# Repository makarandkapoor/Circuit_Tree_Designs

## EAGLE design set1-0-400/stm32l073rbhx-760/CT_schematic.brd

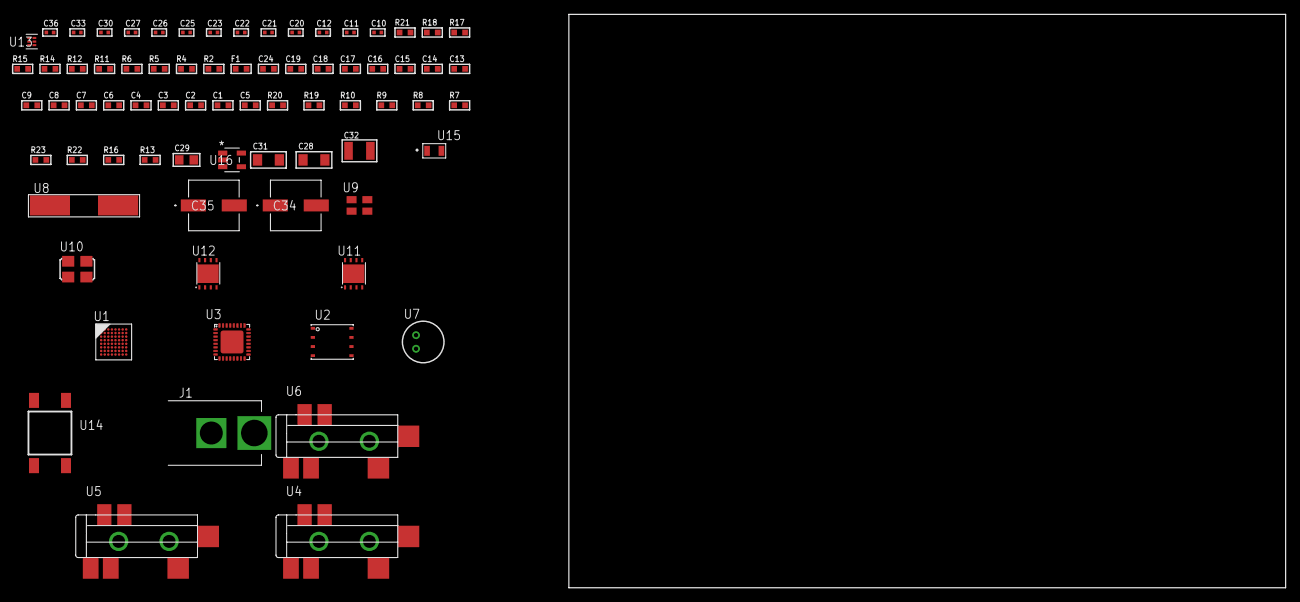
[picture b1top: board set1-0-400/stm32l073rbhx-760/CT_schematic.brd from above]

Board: 2 copper layers, 100.0 x 80.0 mm, 75 parts (0 on the bottom side), 44 nets, no tracks yet.

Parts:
C1, C2, C3, C4, C6, C9: 1e-07; C0603
C5: 4.7e-06; C0603
C7: 1e-08; C0603
C8, C13, C14, C15, C16, C17, C18, C19, C24: 1e-06; C0603
C10, C11: 1e-11; C0402
C12, C25, C26, C27, C30, C36: 1e-08; C0402
C20, C21, C22, C23, C33: 1e-07; C0402
C28, C31: 1e-05; C1206
C29: 1e-05; C0805
C32: 1e-05; C1210
C34, C35: 0.0001; EXV-9H
F1: 240.0; L0603
J1: PJ-037B; PJ-037B_PACKAGE
R2, R15, R18: 1000.0; R0603
R4: 4700.0; R0603
R5, R6: 2200.0; R0603
R7, R8, R9, R10, R19, R20: 10000.0; R0603
R11, R12: 1270.0; R0603
R13, R16: 100000.0; R0603
R14: 200.0; R0603
R17: 2231.0; R0603
R21: 9100.0; R0603
R22: 680000.0; R0603
R23: 120000.0; R0603
U1: STM32L073RBH6; TFBGA64
U2: 24AA256-I/MF; DFN8-S
U3: SGTL5000XNAA3; QFN-32
U4, U5, U6: SJ-43515TS-SMT-TR
U7: WM-64PCT; WM-64PC
U8: ABLS-25.000MHZ-B2F-T
U9: ASEK-32.768KHz-ECST; ASEK
U10: ASFL-24.57MHZ-NCS; ASFL1
U11, U12: LP3878SDX-ADJ/NOPB; WSON-8
U13: TPS3895ADRYR; SON-6
U14: 4-1437565-2; SW_4-1437565-2
U15: Q65110A2395; LGM67K-G1J2-24-Z
U16: nc7sz125m5x; NC7SZ125M5X

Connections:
CLK_CRYSTAL_U1_C1: C10.1, U1.C1, U8.1
CLK_CRYSTAL_U1_D1: C11.1, U1.D1, U8.2
CLK_U1_A1: U1.A1, U9.3
CLK_U3_21: U3.21, U10.3
GND: C1.2, C2.2, C3.2, C4.2, C5.2, C6.2, C7.2, C8.2, C9.2, C10.2, C11.2, C12.2, C20.2, C21.2, C22.2, C23.2, C24.2, C25.2, C26.2, C27.2, C28.2, C29.2, C30.2, C31.2, C32.2, C33.2, C34.2, C35.2, C36.2, J1.2, R2.2, R7.2, R8.2, R9.2, R12.2, R15.2, R18.2, R21.2, R23.2, U1.C2, U1.D4, U1.D5, U1.D6, U1.F1, U2.4, U3.1, U3.3, U3.7, U3.EXP, U5.1, U6.1, U7.2, U9.2, U10.2, U11.3, U11.PAD, U12.3, U12.PAD, U13.2, U15.C, U16.1, U16.3
NET_U1_A3: R6.1, U1.A3, U2.5
NET_U1_B2: C6.1, U1.B2
NET_U1_B3: R5.1, U1.B3, U2.6
NET_U1_B4: R7.1, U1.B4
NET_U1_E1: R4.1, U1.E1, U16.4
NET_U1_H1: C7.1, C8.1, F1.1, U1.G1, U1.H1
NET_U1_H7: U14.3, U14.4
NET_U2_1: R8.1, U2.1
NET_U2_2: R9.1, U2.2
NET_U2_3: R10.1, U2.3
NET_U3_10: C23.1, U3.10
NET_U3_29: R11.1, U3.29
NET_U3_31: R12.1, U3.31
NET_U4_1: U3.4, U4.1
NET_U4_2: U3.2, U4.2
NET_U4_5: U3.6, U4.5
NET_U5_2: C14.1, U5.2
NET_U5_5: C13.1, U5.5
NET_U6_2: C16.1, C17.1, U6.2
NET_U6_5: C15.1, U6.5
NET_U6_13: C16.2, C17.2
NET_U7_1: C18.1, C19.1, C24.1, U3.16, U7.1
NET_U7_15: C18.2, C19.2
NET_U11_1: C27.1, U11.1
NET_U11_6: R14.2, R15.1, U11.6
NET_U11_8: R13.1, U11.8
NET_U12_1: C30.1, U12.1
NET_U12_6: R17.2, R18.1, U12.6
NET_U12_8: R16.1, U12.8
NET_U13_1: R20.1, R21.1, U13.1
NET_U13_3: R22.2, R23.1, U13.3
NET_U13_4: R19.1, U13.4, U16.2
NET_U14_1: R2.1, U14.1, U14.2
PROC_I2S2_CK: U1.G8, U3.24
PROC_I2S2_SD: U1.F7, U3.26
PROC_I2S2_WS: U1.H8, U3.23
VCC_S1_7V5: C28.1, C31.1, C34.1, C35.1, J1.1, R13.2, R16.2, U11.4, U12.4
VCC_TIER1_1V2: C20.1, C29.1, R14.1, U3.30, U11.5
VCC_TIER1_3V3: C1.1, C2.1, C3.1, C4.1, C5.1, C9.1, C12.1, C21.1, C22.1, C25.1, C26.1, C32.1, C33.1, C36.1, F1.2, R4.2, R5.2, R6.2, R10.2, R11.2, R17.1, R19.2, R20.2, R22.1, U1.D2, U1.E4, U1.E5, U1.E6, U2.7, U2.8, U3.5, U3.20, U9.4, U10.4, U12.5, U13.6, U16.5

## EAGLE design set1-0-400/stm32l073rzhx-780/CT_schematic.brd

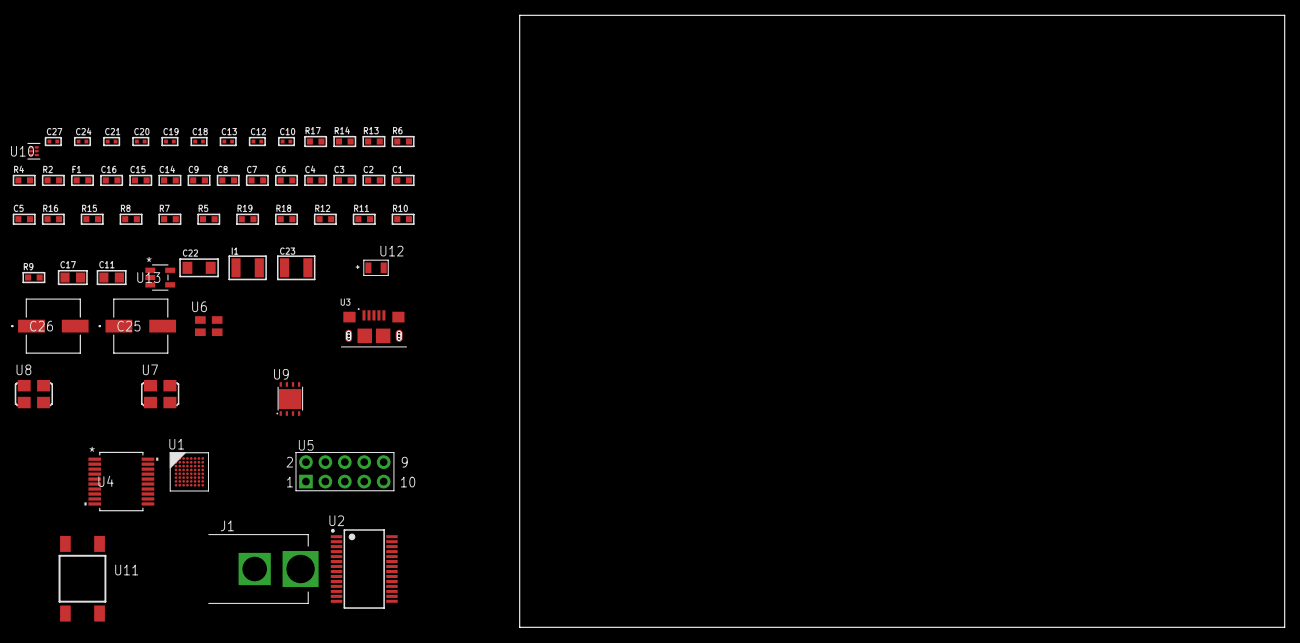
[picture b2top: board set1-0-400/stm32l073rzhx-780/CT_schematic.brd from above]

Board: 2 copper layers, 122.6 x 80.0 mm, 60 parts (0 on the bottom side), 44 nets, no tracks yet.

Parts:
C1, C2, C3, C4, C6, C9: 1e-07; C0603
C5: 4.7e-06; C0603
C7: 1e-08; C0603
C8, C14, C15, C16: 1e-06; C0603
C10, C12, C13, C24: 1e-07; C0402
C11, C17: 4.7e-06; C0805
C18, C19, C20, C21, C27: 1e-08; C0402
C22: 1e-05; C1206
C23: 1e-05; C1210
C25, C26: 0.0001; EXV-9H
F1: 240.0; L0603
I1: 1.5e-05; L1210
J1: PJ-037B; PJ-037B_PACKAGE
R2, R14: 1000.0; R0603
R4, R6: 4700.0; R0603
R5, R7, R8, R15, R16: 10000.0; R0603
R9, R10, R11, R12: 100000.0; R0603
R13: 2231.0; R0603
R17: 9100.0; R0603
R18: 680000.0; R0603
R19: 120000.0; R0603
U1: STM32L073RZH6; TFBGA64
U2: FT232RL-REEL; SSOP-28
U3: 10118193-0001LF; FCI_10118193-0001LF
U4: MAX3218EAP+T; SSOP-20
U5: HTSS-105-01-G-D
U6: ASEK-32.768KHz-ECST; ASEK
U7: ASFL1-12MHZ-NCS; ASFL1
U8: ASFL1-25MHZ-NCS; ASFL1
U9: LP3878SDX-ADJ/NOPB; WSON-8
U10: TPS3895ADRYR; SON-6
U11: 4-1437565-2; SW_4-1437565-2
U12: Q65110A2395; LGM67K-G1J2-24-Z
U13: nc7sz125m5x; NC7SZ125M5X

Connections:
CLK_U1_A1: U1.A1, U6.3
CLK_U1_C1: U1.C1, U8.3
CLK_U2_27: U2.27, U7.3
GND: C1.2, C2.2, C3.2, C4.2, C5.2, C6.2, C7.2, C8.2, C9.2, C10.2, C11.2, C12.2, C13.2, C14.2, C15.2, C16.2, C18.2, C19.2, C20.2, C21.2, C22.2, C23.2, C24.2, C25.2, C26.2, C27.2, J1.2, R2.2, R5.2, R8.2, R14.2, R17.2, R19.2, U1.C2, U1.D4, U1.D5, U1.D6, U1.F1, U2.7, U2.18, U2.21, U2.25, U2.26, U3.5, U3.6, U3.7, U3.8, U3.9, U4.5, U4.17, U4.20, U5.9, U6.2, U7.2, U8.2, U9.3, U9.PAD, U10.2, U12.C, U13.1, U13.3
NET_U1_B2: C6.1, U1.B2
NET_U1_B4: R5.1, U1.B4
NET_U1_E1: R4.1, U1.E1, U13.4
NET_U1_H1: C7.1, C8.1, F1.1, U1.G1, U1.H1
NET_U1_H8: U11.3, U11.4
NET_U2_14: R7.1, U2.14
NET_U2_17: C12.1, U2.17
NET_U2_19: R8.1, U2.19
NET_U3_1: R6.1, U3.1
NET_U3_2: U2.16, U3.2
NET_U3_3: U2.15, U3.3
NET_U4_1: I1.1, U4.1
NET_U4_2: R9.1, U4.2
NET_U4_3: R10.1, U4.3
NET_U4_4: R11.1, U4.4
NET_U4_15: C16.1, U4.15
NET_U4_16: C17.2, U4.16
NET_U4_18: C17.1, U4.18
NET_U4_19: C15.1, U4.19
NET_U5_3: U4.12, U5.3
NET_U5_4: U4.11, U5.4
NET_U5_5: U4.14, U5.5
NET_U5_6: U4.13, U5.6
NET_U9_1: C21.1, U9.1
NET_U9_6: R13.2, R14.1, U9.6
NET_U9_8: R12.1, U9.8
NET_U10_1: R16.1, R17.1, U10.1
NET_U10_3: R18.2, R19.1, U10.3
NET_U10_4: R15.1, U10.4, U13.2
NET_U11_1: R2.1, U11.1, U11.2
PROC_LPUART1_CTS: U1.G4, U4.8
PROC_LPUART1_RTS: U1.B5, U4.10
PROC_LPUART1_RX: U1.A8, U4.9
PROC_LPUART1_TX: U1.A7, U4.7
PROC_USART1_CTS: U1.A4, U2.3
PROC_USART1_RTS: U1.A5, U2.11
PROC_USART1_RX: U1.C3, U2.1
PROC_USART1_TX: U1.C7, U2.5
VCC_S1_6V6: C22.1, C25.1, C26.1, J1.1, R12.2, U9.4
VCC_TIER1_3V3: C1.1, C2.1, C3.1, C4.1, C5.1, C9.1, C10.1, C11.1, C13.1, C14.1, C18.1, C19.1, C20.1, C23.1, C24.1, C27.1, F1.2, I1.2, R4.2, R7.2, R9.2, R10.2, R11.2, R13.1, R15.2, R16.2, R18.1, U1.D2, U1.E4, U1.E5, U1.E6, U2.4, U2.20, U4.6, U6.4, U7.4, U8.4, U9.5, U10.6, U13.5

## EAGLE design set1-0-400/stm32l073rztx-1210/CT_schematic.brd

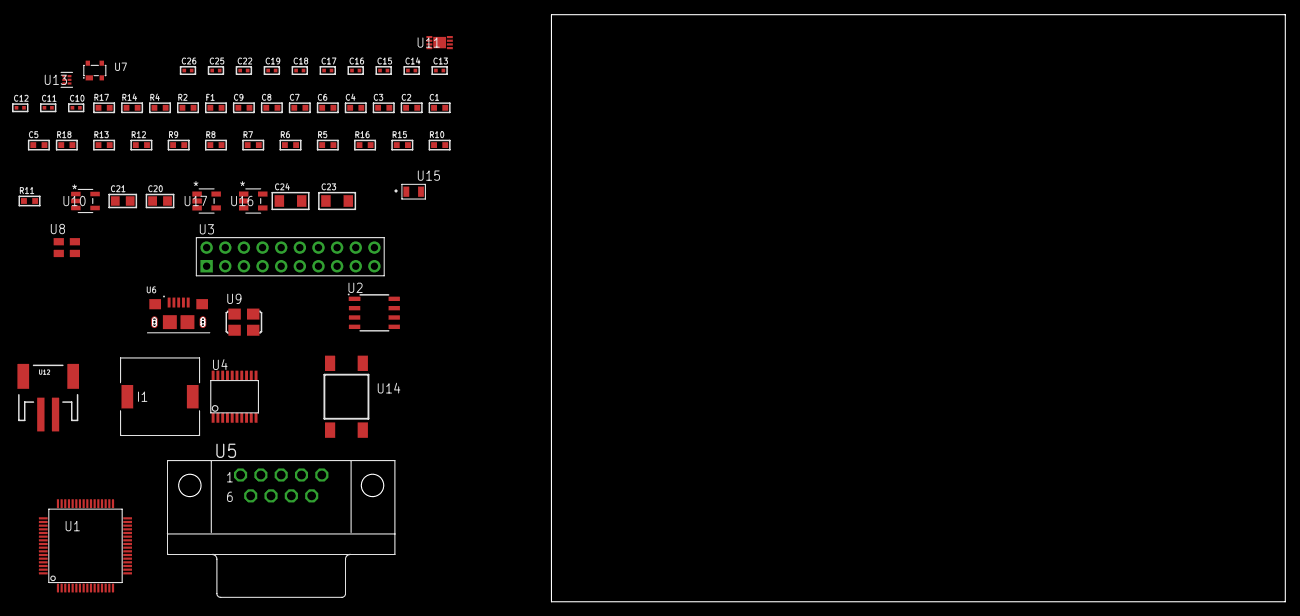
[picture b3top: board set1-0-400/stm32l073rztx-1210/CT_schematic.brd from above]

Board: 2 copper layers, 61 parts (0 on the bottom side), 45 nets, no tracks yet.

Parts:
C1, C2, C3, C4, C6, C9: 1e-07; C0603
C5: 4.7e-06; C0603
C7: 1e-08; C0603
C8: 1e-06; C0603
C10, C18, C19, C25, C26: 1e-08; C0402
C11, C12, C13, C14, C15, C16, C17, C22: 1e-07; C0402
C20, C21: 1e-05; C0805
C23, C24: 1e-05; C1206
F1: 240.0; L0603
I1: 5.2e-06; DR1040
R2: 1000.0; R0603
R4: 4700.0; R0603
R5, R6, R7, R8, R9, R12, R13, R18: 10000.0; R0603
R10: 220000.0; R0603
R11: 1000000.0; R0603
R14: 9100.0; R0603
R15: 680000.0; R0603
R16: 120000.0; R0603
R17: 2000.0; R0603
U1: STM32L073RZT6; LQFP64
U2: AT25128B-SSHL-T; SOIC-8
U3: TST-110-05-T-D-RA
U4: SP3203ECY-L/TR; TSSOP20-I
U5: 182-009-113R531; 182-009-MALE
U6: 10118193-0001LF; FCI_10118193-0001LF
U7: prtr5v0u2ax; SOT143B
U8: ASEK-32.768KHz-ECST; ASEK
U9: ASFL1-25MHZ-NCS; ASFL1
U10: ltc3406es5; TSOT-23-5
U11: MCP73831T-2ACI/MC; DFN8_2X3MC
U12: S2B-PH-SM4-TB(LF)(SN); JST-2-SMD
U13: TPS3895ADRYR; SON-6
U14: 4-1437565-2; SW_4-1437565-2
U15: Q65110A2395; LGM67K-G1J2-24-Z
U16, U17: nc7sz125m5x; NC7SZ125M5X

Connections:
CLK_U1_3: U1.3, U8.3
CLK_U1_5: U1.5, U9.3
GND: C1.2, C2.2, C3.2, C4.2, C5.2, C6.2, C7.2, C8.2, C9.2, C10.2, C11.2, C12.2, C13.2, C16.2, C17.2, C18.2, C19.2, C20.2, C21.1, C21.2, C22.2, C23.2, C24.2, C25.2, C26.2, R2.2, R5.2, R10.2, R14.2, R16.2, R17.2, U1.12, U1.18, U1.31, U1.47, U1.63, U2.4, U3.4, U3.6, U3.8, U3.10, U3.12, U3.14, U3.16, U3.18, U3.20, U4.18, U5.5, U6.5, U6.6, U6.7, U6.8, U6.9, U7.1, U8.2, U9.2, U10.2, U11.6, U11.9, U12.2, U13.2, U15.C, U16.2, U16.3, U17.1, U17.3
INPUT_USBPOWER_5V: C23.1, R18.2, U6.1, U7.4, U11.1, U11.2
NET_U1_1: C6.1, U1.1
NET_U1_7: R4.1, U1.7, U17.4
NET_U1_13: C7.1, C8.1, F1.1, U1.13
NET_U1_60: R5.1, U1.60
NET_U1_62: U14.3, U14.4
NET_U2_3: R6.1, U2.3
NET_U2_7: R8.1, U2.7
NET_U4_1: C14.1, U4.1
NET_U4_2: C16.1, U4.2
NET_U4_3: C14.2, U4.3
NET_U4_4: C15.1, U4.4
NET_U4_5: C15.2, U4.5
NET_U4_6: C17.1, U4.6
NET_U5_2: U4.14, U5.2
NET_U5_3: U4.17, U5.3
NET_U5_7: U4.13, U5.7
NET_U5_8: U4.16, U5.8
NET_U10_3: I1.1, U10.3
NET_U10_5: R10.1, R11.1, U10.5
NET_U10_ATNET_3: I1.2, R11.2
NET_U11_5: R18.1, U11.5
NET_U11_8: R17.1, U11.8
NET_U13_1: R13.1, R14.1, U13.1
NET_U13_3: R15.2, R16.1, U13.3
NET_U13_4: R12.1, U13.4, U16.4, U17.2
NET_U14_1: R2.1, U14.1, U14.2
PROC_LPUART1_CTS: U1.22, U4.8
PROC_LPUART1_RTS: U1.27, U4.10
PROC_LPUART1_RX: U1.8, U4.11
PROC_LPUART1_TX: U1.9, U4.7
PROC_SPI1_MISO: U1.56, U2.2
PROC_SPI1_MOSI: U1.23, U2.5
PROC_SPI1_NSS: R7.1, U1.20, U2.1
PROC_SPI1_SCK: U1.21, U2.6
PROC_SYS_SWCLK: U1.49, U3.9
PROC_SYS_SWDIO: U1.46, U3.7
PROC_USB_DM: U6.2, U7.3
PROC_USB_DP: U6.3, U7.2
RST_OUT_U3_SRESET_B: R9.1, U3.15, U16.1
VCC_S1_3V7: C20.1, C24.1, U10.4, U11.3, U11.4, U12.1
VCC_TIER1_3V3: C1.1, C2.1, C3.1, C4.1, C5.1, C9.1, C10.1, C11.1, C12.1, C13.1, C18.1, C19.1, C21.2, C22.1, C25.1, C26.1, F1.2, I1.2, R4.2, R6.2, R7.2, R8.2, R9.2, R11.2, R12.2, R13.2, R15.1, U1.19, U1.32, U1.48, U1.64, U2.8, U3.1, U4.12, U4.19, U8.4, U9.4, U13.6, U16.5, U17.5

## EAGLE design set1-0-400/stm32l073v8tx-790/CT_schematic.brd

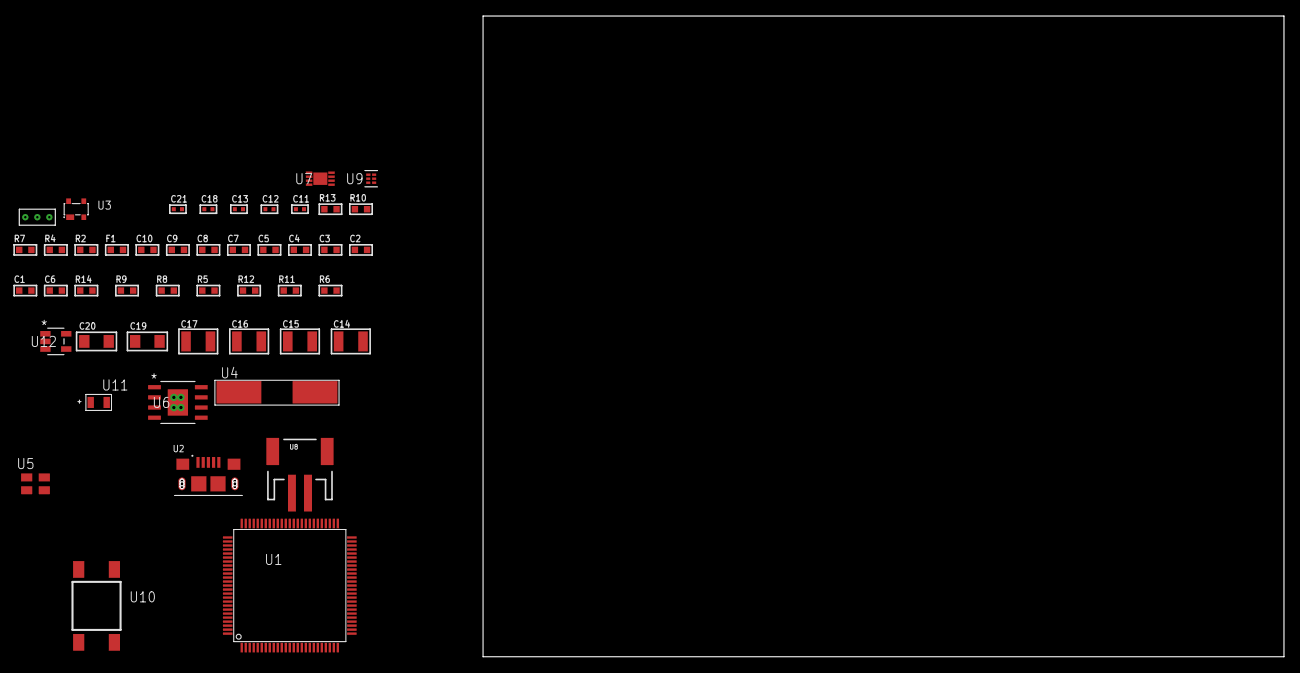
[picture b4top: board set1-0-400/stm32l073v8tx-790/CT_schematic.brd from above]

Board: 2 copper layers, 47 parts (0 on the bottom side), 23 nets, no tracks yet.

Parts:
C1, C2, C3, C4, C5, C7, C10: 1e-07; C0603
C6: 4.7e-06; C0603
C8: 1e-08; C0603
C9: 1e-06; C0603
C11, C12: 1e-11; C0402
C13, C21: 1e-08; C0402
C14, C15, C16, C17: 1e-05; C1210
C18: 1e-07; C0402
C19, C20: 1e-05; C1206
F1: 240.0; L0603
R2: 1000.0; R0603
R4: 4700.0; R0603
R5, R8, R9, R14: 10000.0; R0603
R6: 4031.5447154472; R0603
R7: 2200.0; R0603
R10: 9100.0; R0603
R11: 680000.0; R0603
R12: 120000.0; R0603
R13: 2000.0; R0603
U1: STM32L073V8T6; LQFP100
U2: 10118193-0001LF; FCI_10118193-0001LF
U3: prtr5v0u2ax; SOT143B
U4: ABLS-25.000MHZ-B2F-T
U5: ASEK-32.768KHz-ECST; ASEK
U6: MIC5234YME; SOIC-8_EP
U7: MCP73831T-2ACI/MC; DFN8_2X3MC
U8: S2B-PH-SM4-TB(LF)(SN); JST-2-SMD
U9: TPS3895ADRYR; SON-6
U10: 4-1437565-2; SW_4-1437565-2
U11: Q65110A2395; LGM67K-G1J2-24-Z
U12: nc7sz125m5x; NC7SZ125M5X
U13: Dummy; DUMMY_PACKAGE_102

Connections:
CLK_CRYSTAL_U1_12: C11.1, U1.12, U4.1
CLK_CRYSTAL_U1_13: C12.1, U1.13, U4.2
CLK_U1_8: U1.8, U5.3
GND: C1.2, C2.2, C3.2, C4.2, C5.2, C6.2, C7.2, C8.2, C9.2, C10.2, C11.2, C12.2, C13.2, C14.2, C15.2, C16.2, C17.2, C18.2, C19.2, C20.2, C21.2, R2.2, R5.2, R7.2, R10.2, R12.2, R13.2, U1.19, U1.20, U1.27, U1.49, U1.74, U1.99, U2.5, U2.6, U2.7, U2.8, U2.9, U3.1, U5.2, U6.7, U6.EPAD, U7.6, U7.9, U8.2, U9.2, U11.C, U12.1, U12.3, U13.1
INPUT_USBPOWER_5V: C19.1, R14.2, U2.1, U3.4, U7.1, U7.2
NET_U1_6: C7.1, U1.6
NET_U1_14: R4.1, U1.14, U12.4
NET_U1_22: C8.1, C9.1, F1.1, U1.21, U1.22
NET_U1_94: R5.1, U1.94
NET_U1_98: U10.3, U10.4
NET_U6_4: R6.2, R7.1, U6.4
NET_U7_5: R14.1, U7.5
NET_U7_8: R13.1, U7.8
NET_U9_1: R9.1, R10.1, U9.1
NET_U9_3: R11.2, R12.1, U9.3
NET_U9_4: R8.1, U9.4, U12.2
NET_U10_1: R2.1, U10.1, U10.2
PROC_ADC_IN3: U1.26, U13.3
PROC_ADC_IN13: U1.18, U13.2
PROC_USB_DM: U1.70, U2.2, U3.3
PROC_USB_DP: U1.71, U2.3, U3.2
VCC_S1_3V7: C14.1, C15.1, C20.1, U6.5, U6.8, U7.3, U7.4, U8.1
VCC_TIER1_3V3: C1.1, C2.1, C3.1, C4.1, C5.1, C6.1, C10.1, C13.1, C16.1, C17.1, C18.1, C21.1, F1.2, R4.2, R6.1, R8.2, R9.2, R11.1, U1.28, U1.50, U1.73, U1.75, U1.100, U5.4, U6.1, U9.6, U12.5

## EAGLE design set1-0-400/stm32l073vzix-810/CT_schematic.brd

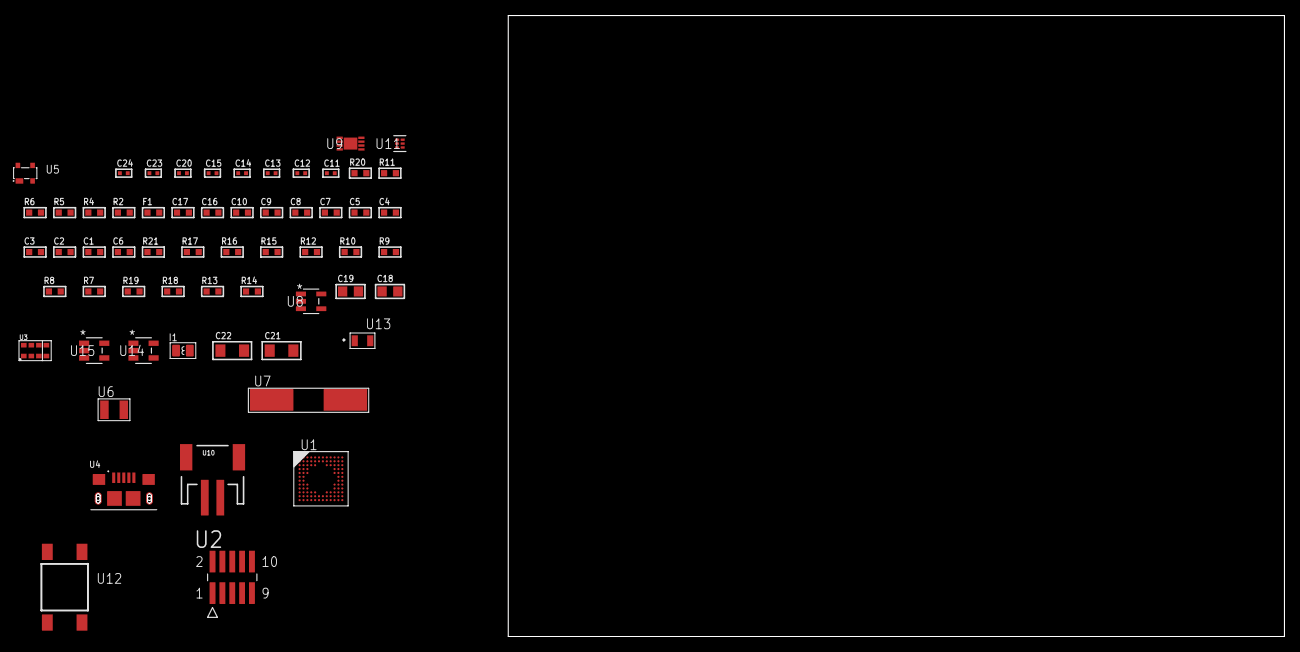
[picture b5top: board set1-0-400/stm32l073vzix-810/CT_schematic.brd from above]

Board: 2 copper layers, 153.1 x 80.0 mm, 60 parts (0 on the bottom side), 31 nets, no tracks yet.

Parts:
C1, C2, C3, C4, C5, C7, C10: 1e-07; C0603
C6: 4.7e-06; C0603
C8: 1e-08; C0603
C9, C16, C17: 1e-06; C0603
C11, C12, C13, C14: 1e-11; C0402
C15, C20: 1e-07; C0402
C18, C19: 1e-05; C0805
C21, C22: 1e-05; C1206
C23, C24: 1e-08; C0402
F1: 240.0; L0603
I1: 3.3e-06; L0806
R2: 1000.0; R0603
R4: 4700.0; R0603
R5, R6: 2200.0; R0603
R7, R8, R9, R10, R12, R15, R16, R21: 10000.0; R0603
R11: 5.0; R0603
R13: 245000.0; R0603
R14: 1000000.0; R0603
R17: 11000.0; R0603
R18: 620000.0; R0603
R19: 120000.0; R0603
R20: 2000.0; R0603
U1: STM32L073VZI6; UFBGA100
U2: FTSH-105-01-L-DV-K; SAMTEC_FTSH-105-01-L-DV-K
U3: TMD27711; SMD-8
U4: 10118193-0001LF; FCI_10118193-0001LF
U5: prtr5v0u2ax; SOT143B
U6: ABS07-32.768KHZ-7-T
U7: ABLS-25.000MHZ-B2F-T
U8: ltc3406es5; TSOT-23-5
U9: MCP73831T-2ACI/MC; DFN8_2X3MC
U10: S2B-PH-SM4-TB(LF)(SN); JST-2-SMD
U11: TPS3895ADRYR; SON-6
U12: 4-1437565-2; SW_4-1437565-2
U13: Q65110A2395; LGM67K-G1J2-24-Z
U14, U15: nc7sz125m5x; NC7SZ125M5X

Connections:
CLK_CRYSTAL_U1_D1: C11.1, U1.D1, U6.1
CLK_CRYSTAL_U1_E1: C12.1, U1.E1, U6.2
CLK_CRYSTAL_U1_F1: C13.1, U1.F1, U7.1
CLK_CRYSTAL_U1_G1: C14.1, U1.G1, U7.2
GND: C1.2, C2.2, C3.2, C4.2, C5.2, C6.2, C7.2, C8.2, C9.2, C10.2, C11.2, C12.2, C13.2, C14.2, C15.2, C16.2, C17.2, C18.2, C19.1, C19.2, C20.2, C21.2, C22.2, C23.2, C24.2, R2.2, R7.2, R11.2, R13.2, R17.2, R19.2, R20.2, U1.D3, U1.E3, U1.F11, U1.F12, U1.J1, U1.K1, U2.3, U2.5, U3.3, U4.5, U4.6, U4.7, U4.8, U4.9, U5.1, U8.2, U9.6, U9.9, U10.2, U11.2, U13.C, U14.2, U14.3, U15.1, U15.3
INPUT_USBPOWER_5V: C21.1, R21.2, U4.1, U5.4, U9.1, U9.2
NET_U1_A3: R5.1, U1.A3, U3.2
NET_U1_A4: R7.1, U1.A4
NET_U1_B3: R6.1, U1.B3, U3.8
NET_U1_E2: C7.1, U1.E2
NET_U1_H2: R4.1, U1.H2, U15.4
NET_U1_M1: C8.1, C9.1, F1.1, U1.L1, U1.M1
NET_U1_M12: U12.3, U12.4
NET_U2_9: R11.1, U2.9
NET_U3_7: R12.1, U3.7
NET_U8_3: I1.1, U8.3
NET_U8_5: R13.1, R14.1, U8.5
NET_U8_ATNET_3: I1.2, R14.2
NET_U9_5: R21.1, U9.5
NET_U9_8: R20.1, U9.8
NET_U11_1: R16.1, R17.1, U11.1
NET_U11_3: R18.2, R19.1, U11.3
NET_U11_4: R15.1, U11.4, U14.4, U15.2
NET_U12_1: R2.1, U12.1, U12.2
PROC_SYS_SWCLK: R9.1, U1.A10, U2.4
PROC_SYS_SWDIO: R10.1, U1.A11, U2.2
PROC_USB_DM: U1.B12, U4.2, U5.3
PROC_USB_DP: U1.A12, U4.3, U5.2
RST_OUT_U2_JTAG_RST_B: R8.1, U2.10, U14.1
VCC_S1_3V7: C18.1, C22.1, U8.4, U9.3, U9.4, U10.1
VCC_TIER1_3V0: C1.1, C2.1, C3.1, C4.1, C5.1, C6.1, C10.1, C15.1, C16.1, C17.1, C19.2, C20.1, C23.1, C24.1, F1.2, I1.2, R4.2, R5.2, R6.2, R8.2, R9.2, R10.2, R12.2, R14.2, R15.2, R16.2, R18.1, U1.C4, U1.C11, U1.G11, U1.G12, U1.H3, U2.1, U3.1, U3.4, U11.6, U14.5, U15.5

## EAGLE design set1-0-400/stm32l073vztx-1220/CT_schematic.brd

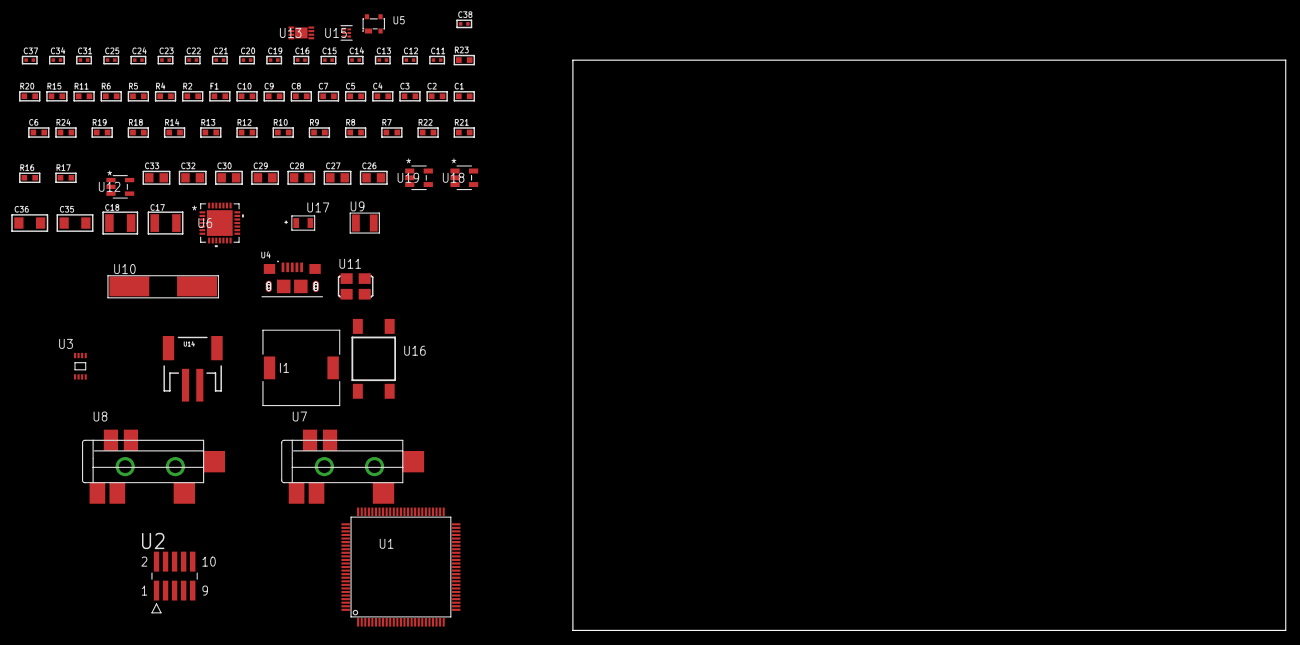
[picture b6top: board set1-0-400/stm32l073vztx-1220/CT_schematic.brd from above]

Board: 2 copper layers, 81 parts (0 on the bottom side), 38 nets, no tracks yet.

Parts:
C1, C2, C3, C4, C5, C7, C10: 1e-07; C0603
C6: 4.7e-06; C0603
C8: 1e-08; C0603
C9: 1e-06; C0603
C11, C12, C13, C14: 1e-11; C0402
C15, C21, C22, C23, C24, C25, C34: 1e-07; C0402
C16, C31, C37, C38: 1e-08; C0402
C17, C18: 2.2e-05; C1210
C19, C20: 1e-09; C0402
C26, C27, C28, C29, C30, C32, C33: 1e-05; C0805
C35, C36: 1e-05; C1206
F1: 240.0; L0603
I1: 5.2e-06; DR1040
R2: 1000.0; R0603
R4: 4700.0; R0603
R5, R6: 2200.0; R0603
R7, R8, R9, R10, R18, R19, R24: 10000.0; R0603
R11: 5.0; R0603
R12, R13, R14: 47000.0; R0603
R15: 680.0; R0603
R16: 220000.0; R0603
R17: 1000000.0; R0603
R20: 9100.0; R0603
R21: 680000.0; R0603
R22: 120000.0; R0603
R23: 2000.0; R0603
U1: STM32L073VZT3; LQFP100
U2: FTSH-105-01-L-DV-K; SAMTEC_FTSH-105-01-L-DV-K
U3: 24AA01T-I/MNY; TDFN-8/6MM
U4: 10118193-0001LF; FCI_10118193-0001LF
U5: prtr5v0u2ax; SOT143B
U6: WM8731CLSEFL; QFN-28
U7, U8: SJ-43515TS-SMT-TR
U9: ABS07-32.768KHZ-7-T
U10: ABLS-25.000MHZ-B2F-T
U11: ASFL1-12.288MHZ-EC-T; ASFL1
U12: ltc3406es5; TSOT-23-5
U13: MCP73831T-2ACI/MC; DFN8_2X3MC
U14: S2B-PH-SM4-TB(LF)(SN); JST-2-SMD
U15: TPS3895ADRYR; SON-6
U16: 4-1437565-2; SW_4-1437565-2
U17: Q65110A2395; LGM67K-G1J2-24-Z
U18, U19: nc7sz125m5x; NC7SZ125M5X

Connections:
CLK_CRYSTAL_U1_8: C11.1, U1.8, U9.1
CLK_CRYSTAL_U1_9: C12.1, U1.9, U9.2
CLK_CRYSTAL_U1_12: C13.1, U1.12, U10.1
CLK_CRYSTAL_U1_13: C14.1, U1.13, U10.2
CLK_U6_1: U6.1, U11.3
GND: C1.2, C2.2, C3.2, C4.2, C5.2, C6.2, C7.2, C8.2, C9.2, C10.2, C11.2, C12.2, C13.2, C14.2, C15.2, C16.2, C20.2, C21.2, C22.2, C23.2, C24.2, C25.2, C26.2, C27.2, C28.2, C29.2, C30.2, C31.2, C32.2, C33.1, C33.2, C34.2, C35.2, C36.2, C37.2, C38.2, R2.2, R7.2, R11.2, R12.2, R13.2, R14.2, R16.2, R20.2, R22.2, R23.2, U1.19, U1.20, U1.27, U1.49, U1.74, U1.99, U2.3, U2.5, U3.4, U3.7, U4.5, U4.6, U4.7, U4.8, U4.9, U5.1, U6.4, U6.15, U6.19, U6.25, U6.26, U6.29, U7.1, U8.1, U11.2, U12.2, U13.6, U13.9, U14.2, U15.2, U17.C, U18.2, U18.3, U19.1, U19.3
INPUT_USBPOWER_5V: C35.1, R24.2, U4.1, U5.4, U13.1, U13.2
NET_U1_6: C7.1, U1.6
NET_U1_14: R4.1, U1.14, U19.4
NET_U1_22: C8.1, C9.1, F1.1, U1.21, U1.22
NET_U1_68: R5.1, U1.68, U3.6
NET_U1_69: R6.1, U1.69, U3.5
NET_U1_94: R7.1, U1.94
NET_U1_98: U16.3, U16.4
NET_U2_9: R11.1, U2.9
NET_U6_20: C25.1, C30.1, U6.20
NET_U7_2: C18.1, R13.1, U7.2
NET_U7_5: C17.1, R12.1, U7.5
NET_U8_5: C19.1, C20.1, R14.1, R15.1, U8.5
NET_U12_3: I1.1, U12.3
NET_U12_5: R16.1, R17.1, U12.5
NET_U12_ATNET_3: I1.2, R17.2
NET_U13_5: R24.1, U13.5
NET_U13_8: R23.1, U13.8
NET_U15_1: R19.1, R20.1, U15.1
NET_U15_3: R21.2, R22.1, U15.3
NET_U15_4: R18.1, U15.4, U18.4, U19.2
NET_U16_1: R2.1, U16.1, U16.2
PROC_I2S2_CK: U1.52, U6.7
PROC_I2S2_SD: U1.18, U6.8
PROC_I2S2_WS: U1.51, U6.9, U6.11
PROC_SYS_SWCLK: R9.1, U1.76, U2.4
PROC_SYS_SWDIO: R10.1, U1.72, U2.2
PROC_USB_DM: U1.70, U4.2, U5.3
PROC_USB_DP: U1.71, U4.3, U5.2
RST_OUT_U2_JTAG_RST_B: R8.1, U2.10, U18.1
VCC_S1_3V7: C32.1, C36.1, U12.4, U13.3, U13.4, U14.1
VCC_TIER1_3V3: C1.1, C2.1, C3.1, C4.1, C5.1, C6.1, C10.1, C15.1, C16.1, C21.1, C22.1, C23.1, C24.1, C26.1, C27.1, C28.1, C29.1, C31.1, C33.2, C34.1, C37.1, C38.1, F1.2, I1.2, R4.2, R5.2, R6.2, R8.2, R9.2, R10.2, R17.2, R18.2, R19.2, R21.1, U1.28, U1.50, U1.73, U1.75, U1.100, U2.1, U3.8, U6.3, U6.5, U6.12, U6.18, U11.4, U15.6, U18.5, U19.5

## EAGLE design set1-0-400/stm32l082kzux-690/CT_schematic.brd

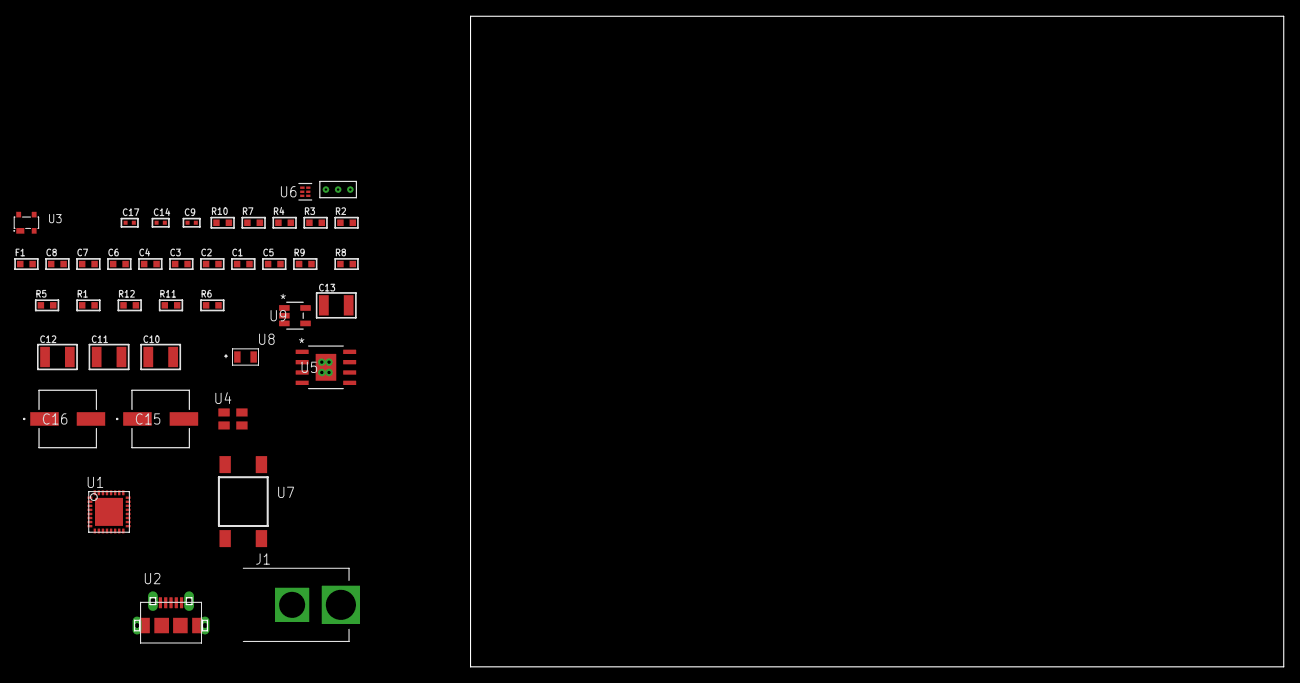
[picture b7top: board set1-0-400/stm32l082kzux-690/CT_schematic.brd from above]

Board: 2 copper layers, 41 parts (0 on the bottom side), 19 nets, no tracks yet.

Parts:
C1, C2, C3, C4, C8: 1e-07; C0603
C5: 4.7e-06; C0603
C6: 1e-08; C0603
C7: 1e-06; C0603
C9, C17: 1e-08; C0402
C10, C11, C12, C13: 1e-05; C1210
C14: 1e-07; C0402
C15, C16: 0.0001; EXV-9H
F1: 240.0; L0603
J1: PJ-037B; PJ-037B_PACKAGE
R1, R5, R8, R9: 10000.0; R0603
R2: 1000.0; R0603
R3: 1600.5; R0603
R4: 4700.0; R0603
R6: 4031.5447154472; R0603
R7: 2200.0; R0603
R10: 9100.0; R0603
R11: 680000.0; R0603
R12: 120000.0; R0603
U1: STM32L082KZU6; UFQFPN32
U2: 47590-0001; MICRO_USB_AB
U3: prtr5v0u2ax; SOT143B
U4: ASEK-32.768KHz-ECST; ASEK
U5: MIC5234YME; SOIC-8_EP
U6: TPS3895ADRYR; SON-6
U7: 4-1437565-2; SW_4-1437565-2
U8: Q65110A2395; LGM67K-G1J2-24-Z
U9: nc7sz125m5x; NC7SZ125M5X
U10: Dummy; DUMMY_PACKAGE_82

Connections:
CLK_U1_1: U1.1, U4.3
GND: C1.2, C2.2, C3.2, C4.2, C5.2, C6.2, C7.2, C8.2, C9.2, C10.2, C11.2, C12.2, C13.2, C14.2, C15.2, C16.2, C17.2, J1.2, R2.2, R5.2, R7.2, R10.2, R12.2, U1.4, U1.16, U1.31, U1.EPAD, U2.5, U2.6, U2.7, U2.8, U2.9, U3.1, U4.2, U5.7, U5.EPAD, U6.2, U8.C, U9.1, U9.3, U10.1
NET_U1_3: R4.1, U1.3, U9.4
NET_U1_5: C6.1, C7.1, F1.1, U1.5
NET_U1_28: R3.1, U1.28, U8.A
NET_U1_29: R1.1, U1.29, U7.3, U7.4
NET_U1_30: R5.1, U1.30
NET_U3_4: U2.1, U3.4
NET_U5_4: R6.2, R7.1, U5.4
NET_U6_1: R9.1, R10.1, U6.1
NET_U6_3: R11.2, R12.1, U6.3
NET_U6_4: R8.1, U6.4, U9.2
NET_U7_1: R2.1, U7.1, U7.2
PROC_TIM2_CH1: U1.6, U10.3
PROC_TIM2_CH3: U1.8, U10.2
PROC_USB_DM: U1.21, U2.2, U3.3
PROC_USB_DP: U1.22, U2.3, U3.2
VCC_S1_5V7: C10.1, C11.1, C15.1, C16.1, J1.1, U5.5, U5.8
VCC_TIER1_3V3: C1.1, C2.1, C3.1, C4.1, C5.1, C8.1, C9.1, C12.1, C13.1, C14.1, C17.1, F1.2, R1.2, R3.2, R4.2, R6.1, R8.2, R9.2, R11.1, U1.17, U1.24, U1.32, U4.4, U5.1, U6.6, U9.5

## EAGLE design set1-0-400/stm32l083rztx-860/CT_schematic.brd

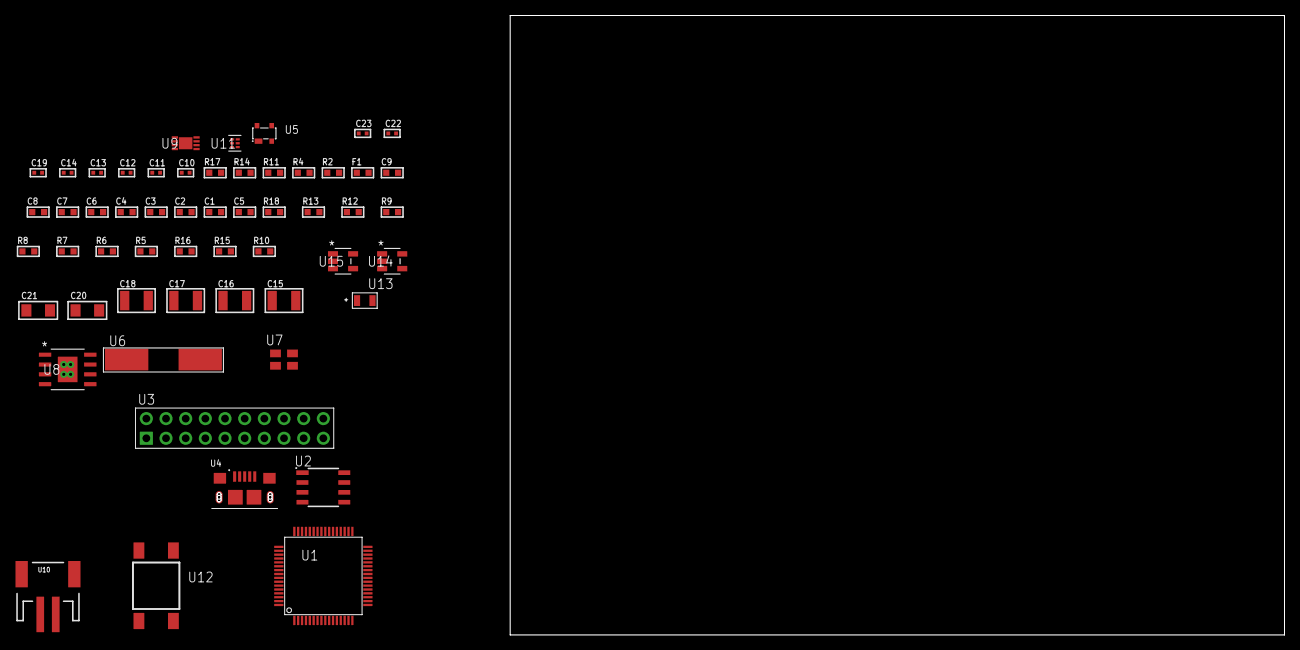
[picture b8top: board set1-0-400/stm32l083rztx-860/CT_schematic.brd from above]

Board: 2 copper layers, 55 parts (0 on the bottom side), 30 nets, no tracks yet.

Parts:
C1, C2, C3, C4, C6, C9: 1e-07; C0603
C5: 4.7e-06; C0603
C7: 1e-08; C0603
C8: 1e-06; C0603
C10, C11: 1e-11; C0402
C12, C14, C22, C23: 1e-08; C0402
C13, C19: 1e-07; C0402
C15, C16, C17, C18: 1e-05; C1210
C20, C21: 1e-05; C1206
F1: 240.0; L0603
R2: 1000.0; R0603
R4: 4700.0; R0603
R5, R6, R7, R8, R9, R12, R13, R18: 10000.0; R0603
R10: 4031.5447154472; R0603
R11: 2200.0; R0603
R14: 9100.0; R0603
R15: 680000.0; R0603
R16: 120000.0; R0603
R17: 2000.0; R0603
U1: STM32L083RZT6; LQFP64
U2: AT25M01-SSHM-T; SOIC-8
U3: TST-110-05-T-D-RA
U4: 10118193-0001LF; FCI_10118193-0001LF
U5: prtr5v0u2ax; SOT143B
U6: ABLS-25.000MHZ-B2F-T
U7: ASEK-32.768KHz-ECST; ASEK
U8: MIC5234YME; SOIC-8_EP
U9: MCP73831T-2ACI/MC; DFN8_2X3MC
U10: S2B-PH-SM4-TB(LF)(SN); JST-2-SMD
U11: TPS3895ADRYR; SON-6
U12: 4-1437565-2; SW_4-1437565-2
U13: Q65110A2395; LGM67K-G1J2-24-Z
U14, U15: nc7sz125m5x; NC7SZ125M5X

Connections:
CLK_CRYSTAL_U1_5: C10.1, U1.5, U6.1
CLK_CRYSTAL_U1_6: C11.1, U1.6, U6.2
CLK_U1_3: U1.3, U7.3
GND: C1.2, C2.2, C3.2, C4.2, C5.2, C6.2, C7.2, C8.2, C9.2, C10.2, C11.2, C12.2, C13.2, C14.2, C15.2, C16.2, C17.2, C18.2, C19.2, C20.2, C21.2, C22.2, C23.2, R2.2, R5.2, R11.2, R14.2, R16.2, R17.2, U1.12, U1.18, U1.31, U1.47, U1.63, U2.4, U3.4, U3.6, U3.8, U3.10, U3.12, U3.14, U3.16, U3.18, U3.20, U4.5, U4.6, U4.7, U4.8, U4.9, U5.1, U7.2, U8.7, U8.EPAD, U9.6, U9.9, U10.2, U11.2, U13.C, U14.2, U14.3, U15.1, U15.3
INPUT_USBPOWER_5V: C20.1, R18.2, U4.1, U5.4, U9.1, U9.2
NET_U1_1: C6.1, U1.1
NET_U1_7: R4.1, U1.7, U15.4
NET_U1_13: C7.1, C8.1, F1.1, U1.13
NET_U1_60: R5.1, U1.60
NET_U1_62: U12.3, U12.4
NET_U2_3: R6.1, U2.3
NET_U2_7: R8.1, U2.7
NET_U8_4: R10.2, R11.1, U8.4
NET_U9_5: R18.1, U9.5
NET_U9_8: R17.1, U9.8
NET_U11_1: R13.1, R14.1, U11.1
NET_U11_3: R15.2, R16.1, U11.3
NET_U11_4: R12.1, U11.4, U14.4, U15.2
NET_U12_1: R2.1, U12.1, U12.2
PROC_SPI1_MISO: U1.22, U2.2
PROC_SPI1_MOSI: U1.23, U2.5
PROC_SPI1_NSS: R7.1, U1.20, U2.1
PROC_SPI1_SCK: U1.21, U2.6
PROC_SYS_SWCLK: U1.49, U3.9
PROC_SYS_SWDIO: U1.46, U3.7
PROC_USB_DM: U1.44, U4.2, U5.3
PROC_USB_DP: U1.45, U4.3, U5.2
RST_OUT_U3_SRESET_B: R9.1, U3.15, U14.1
VCC_S1_3V7: C15.1, C16.1, C21.1, U8.5, U8.8, U9.3, U9.4, U10.1
VCC_TIER1_3V3: C1.1, C2.1, C3.1, C4.1, C5.1, C9.1, C12.1, C13.1, C14.1, C17.1, C18.1, C19.1, C22.1, C23.1, F1.2, R4.2, R6.2, R7.2, R8.2, R9.2, R10.1, R12.2, R13.2, R15.1, U1.19, U1.32, U1.48, U1.64, U2.8, U3.1, U7.4, U8.1, U11.6, U14.5, U15.5
